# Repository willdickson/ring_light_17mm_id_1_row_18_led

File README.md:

# ring_light_17mm_id_1_row_18_led
LED ring light with 17mm inner diameter hole and one row of 18 LEDs.

# License: 
Creative Commons Attribution 4.0 International CC BY 4.0

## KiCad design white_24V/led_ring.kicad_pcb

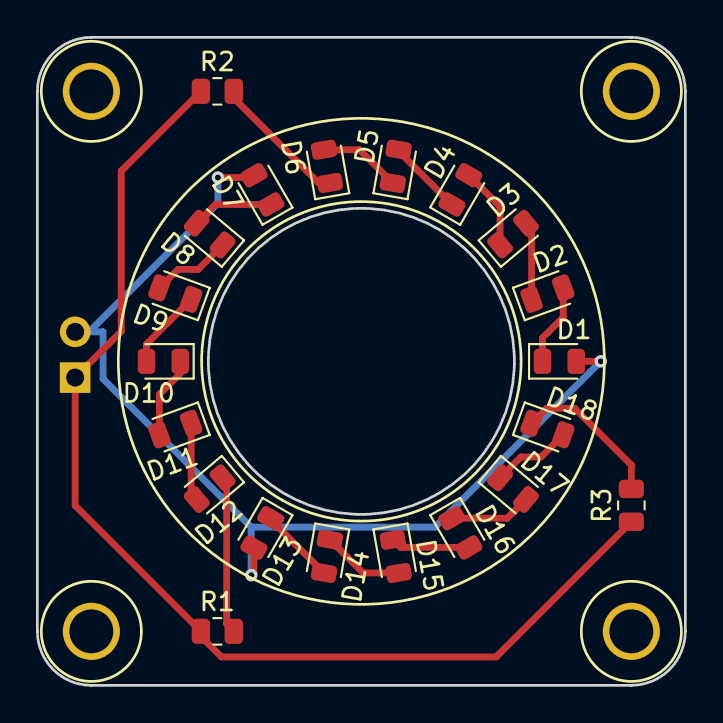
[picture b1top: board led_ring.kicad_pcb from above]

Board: 2 copper layers, 36.0 x 36.0 mm, 26 parts (1 on the bottom side), 20 nets.

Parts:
D1, D2, D3, D4, D5, D6, D7, D8, D9, D10, D11, D12, D13, D14, D15, D16, D17, D18: LED; LED_0805_2012Metric
J1: Conn_01x02; PinHeader_1x02_P2.54mm_Vertical
M1, M2, M3, M4: MOUNT_HOLE_4-40
R1, R2, R3: 402; R_0805_2012Metric

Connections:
GND: J1.1, R1.1, R2.1, R3.1
unnamed: D1.1, D2.2
unnamed: D1.2, D7.2, D13.2, J1.2
unnamed: D2.1, D3.2
unnamed: D3.1, D4.2
unnamed: D4.1, D5.2
unnamed: D5.1, D6.2
unnamed: D6.1, R2.2
unnamed: D7.1, D8.2
unnamed: D8.1, D9.2
unnamed: D10.1, D11.2
unnamed: D9.1, D10.2
unnamed: D11.1, D12.2
unnamed: D12.1, R1.2
unnamed: D13.1, D14.2
unnamed: D14.1, D15.2
unnamed: D15.1, D16.2
unnamed: D16.1, D17.2
unnamed: D17.1, D18.2
unnamed: D18.1, R3.2

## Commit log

2021-09-15 Project creation.
2021-09-15 split project into IR and white LED designs. Created fab files for IR design.
2021-09-15 Finished initial design.
2021-09-15 Added image of PCB.
